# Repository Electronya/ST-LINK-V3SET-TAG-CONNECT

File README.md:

# ST-LINK-V3SET-TAG-CONNECT
ST-LINK-V3SET to TAG-CONNECT adaptor board

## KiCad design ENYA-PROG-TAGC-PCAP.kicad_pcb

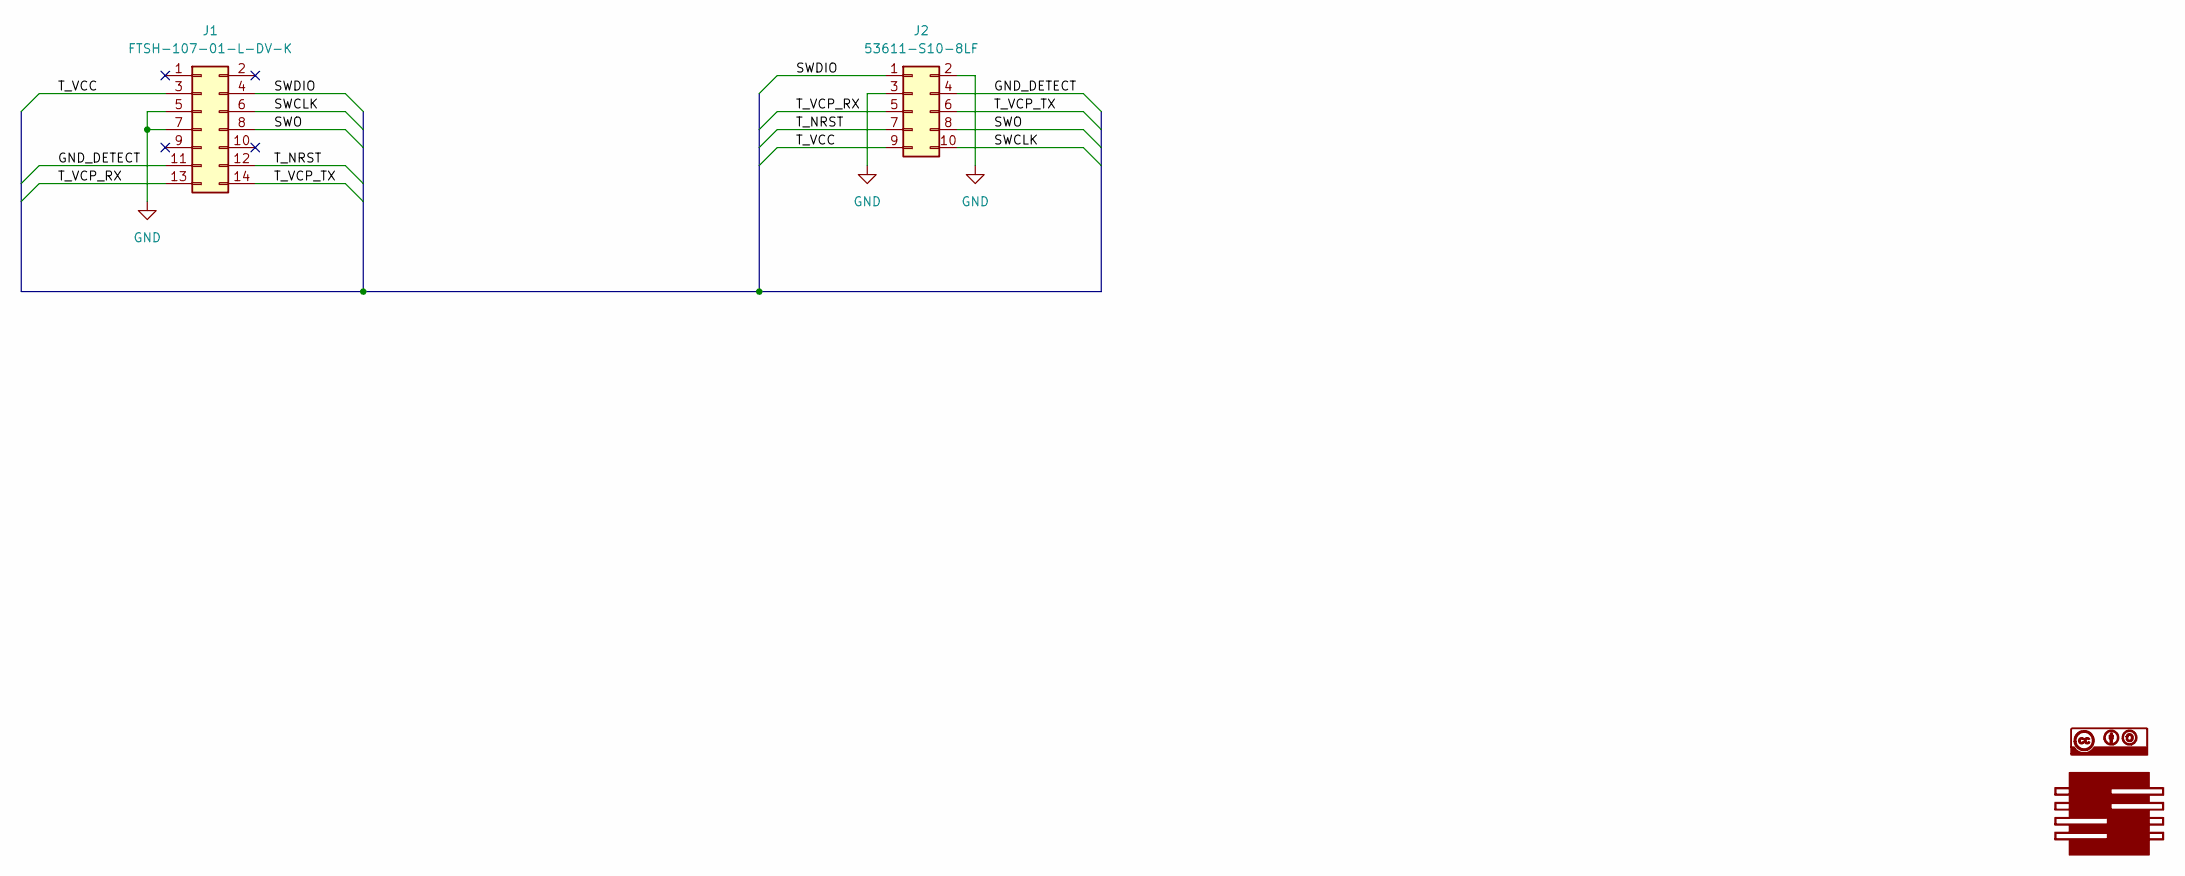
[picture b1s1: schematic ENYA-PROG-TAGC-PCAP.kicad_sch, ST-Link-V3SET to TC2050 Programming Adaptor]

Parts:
G1: Electronya_Logo; Electronya_Logo_12MM
G2: CC-BY-SA_Logo; CC-BY-SA_12MM
J1: FTSH-107-01-L-DV-K; Manufacturer Part Number FTSH-107-01-L-DV-K; Digi-Key Part Number SAM9449-ND
J2: CONN_2x05_MALE_100PITCH_IDC_LATCH; IDC_HEADER_2x05_LATCH_SMD; Manufacturer Part Number 53611-S10-8LF; Digi-Key Part Number 609-53611-S10-8LF-ND

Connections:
/GND_DETECT: J1.11, J2.4
/SWCLK: J1.6, J2.10
/SWDIO: J1.4, J2.1
/SWO: J1.8, J2.8
/T_NRST: J1.12, J2.7
/T_VCC: J1.3, J2.9
/T_VCP_RX: J1.13, J2.5
/T_VCP_TX: J1.14, J2.6
GND: J1.5, J1.7, J2.2, J2.3

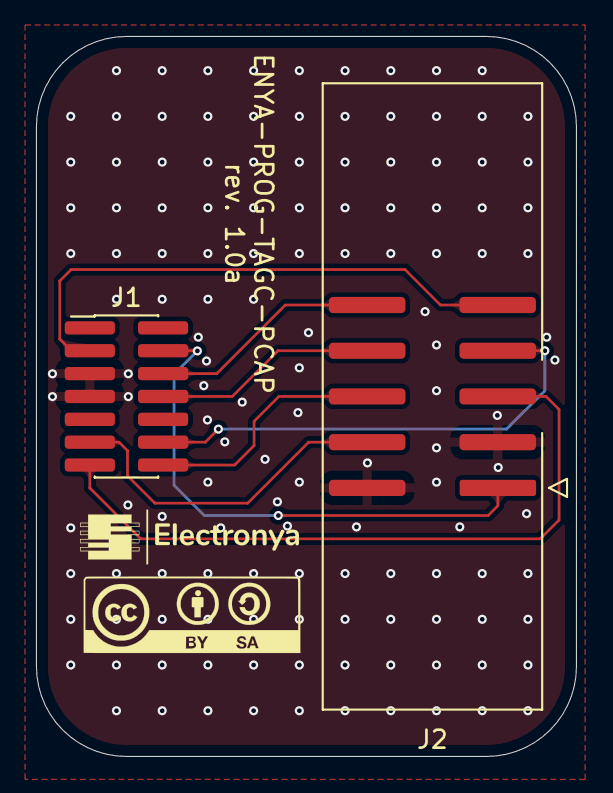
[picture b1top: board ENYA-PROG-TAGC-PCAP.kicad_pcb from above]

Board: 2 copper layers, 30.0 x 40.0 mm, 4 parts (0 on the bottom side), 9 nets.

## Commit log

2024-07-07 first rev

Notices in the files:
parts and their libraries:
CC-BY-SA, creative common
